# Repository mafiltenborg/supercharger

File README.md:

# BP-1A lookalike battery pack: BP-1M
**This is a Work In Progress. It's not even complete!**

If you own a vintage Texas Instruments calculator powered by a BP-1 or BP-1A pack of 3 rechargeable NiCd AA-sized cells in a plastic casing, this repo may be of interest to you.

Because none of these packs have survived the ravages of time, meaning lots of vintage calculators now need replacement battery packs. Yours too?

Here, you find my take on the subject. I've taken inspiration from a design made by Tom LeMense (aka *tomcircuit*) carrying the [CC-BY-SA licence](https://creativecommons.org/cc-licenses/), found here: https://github.com/tomcircuit/TI59_battery

Credit for the casing design goes to him!
The electronics also originate from tomcircuit, albeit in a different form factor and with some tweaks.

## Desired targets
I'm aiming for maximum capacity within the physical constraints given, USB-C charging and an on-off switch on the pack itself.
* Capacity: NiCd pack delivered 500 mAh, giving roughly 3 hours of on-time. I'd like to have a full working-day, meaning at least 1500 mAh.
* USB-C: The current charging standard. Also, the original charger delivers a maximum of 150 mA, leading to a theoretical charging time of at least 10 hours - more likely 'overnight'. Going with something like 500 mA would reduce charging time to 4 or 5 hours in the real world.
* Charging indicator LED. Takes the guesswork out of the refill-process.
* On-off switch: I'd like to take the strain off of the built-in slide switch.
* Charge state indicator; push a button and get indication on a tiny three-colour LED-bar
* Finally, it's dawned on me (greetings go to tomcircuit) that it's possible to make the design so that the calculator can be run off of the OE charger with the pack installed. A combo of practicality and foolproofing; I like that!

## Unachievable, unselected or unwanted targets
* Charging installed pack by means of the OE charger. Possible in theory, but we'd have to accept at least a 10-hour charging period - with the calculator off. Also, I'm doubtful if there's room for the extra circuitry.

## Additional thoughts & ideas
A charging stand to fit the TI59. Should be achievable as the pack's USB-C is pointing straight down. Could also be executed with magnetic pogo-pin-coupling. Hmmm...

## A few specifics on the design
Charger: LTH7R
Charge state display: HM1160

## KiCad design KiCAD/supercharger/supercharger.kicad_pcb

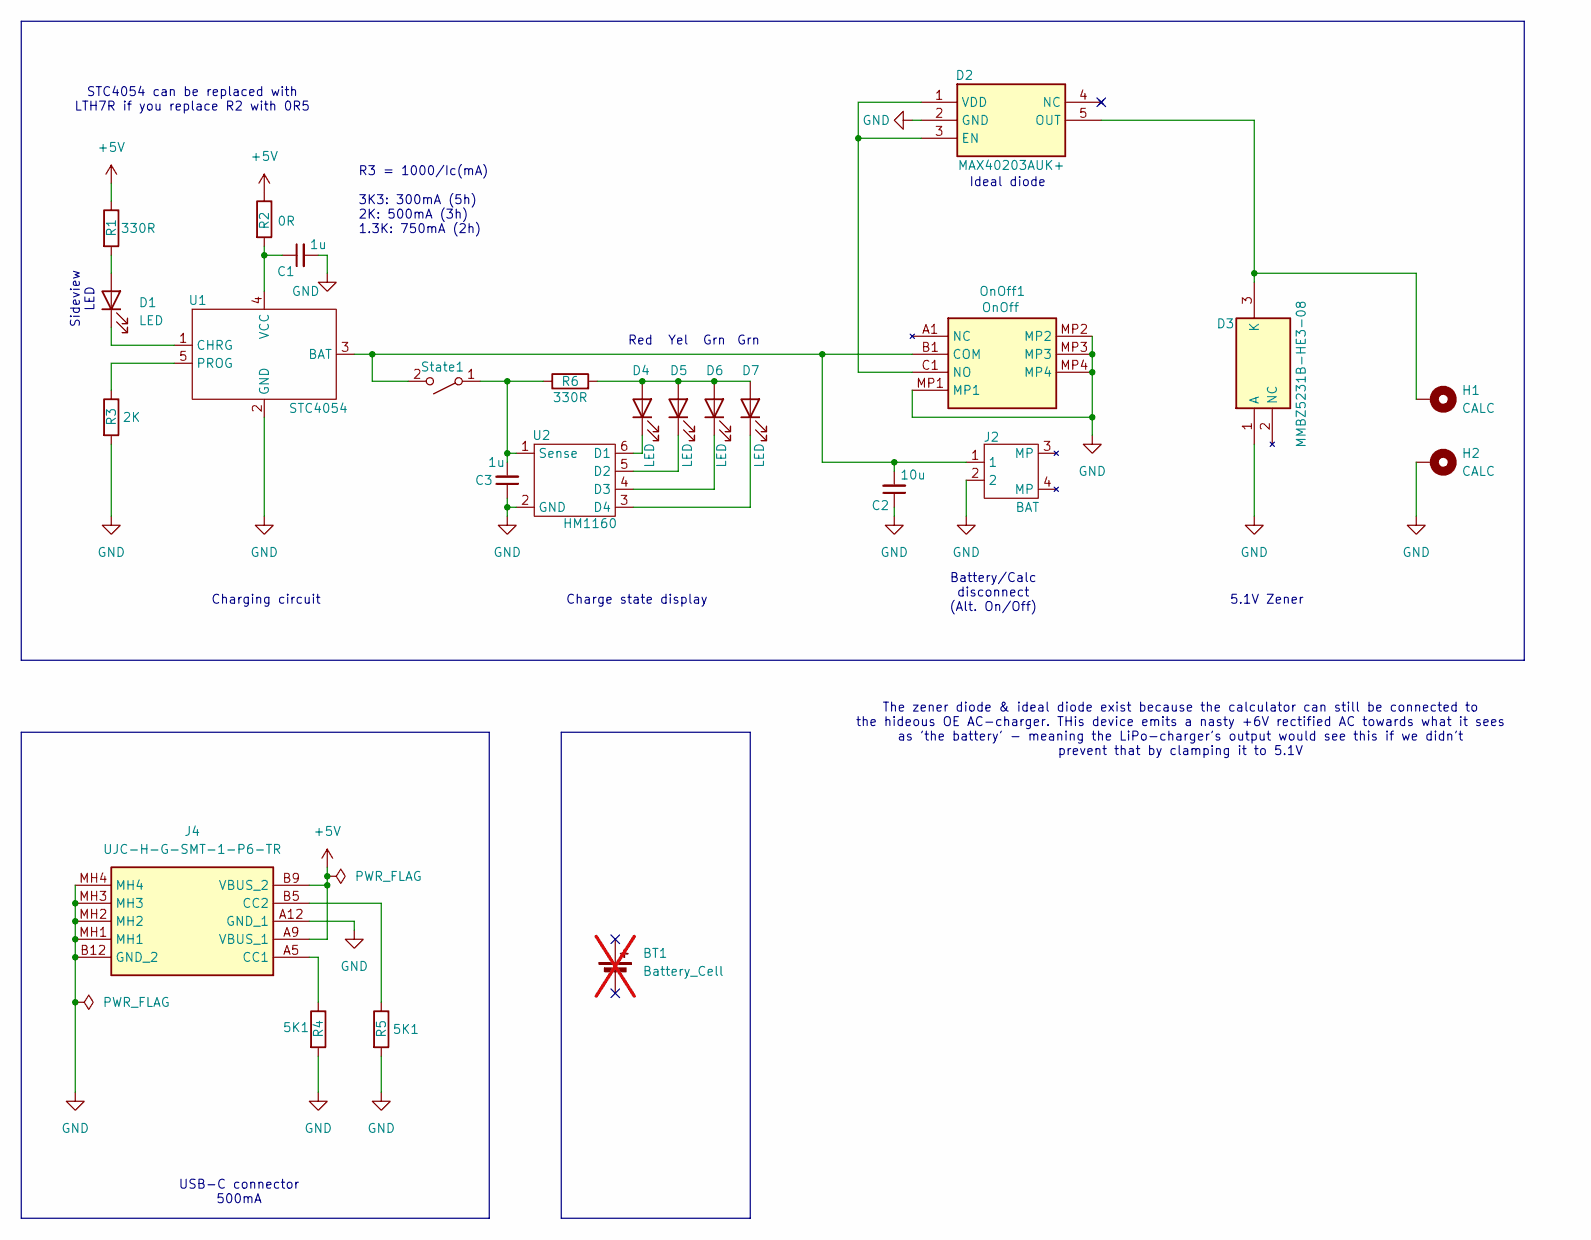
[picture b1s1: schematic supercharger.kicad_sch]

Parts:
BT1: Battery_Cell; not fitted
C1, C3: 1u; C_0603_1608Metric
C2: 10u; C_0603_1608Metric
D1, D4, D5, D6, D7: LED; LED_0603_1608Metric
D2: MAX40203AUK+; SOT-23-5_HandSoldering; Manufacturer_Part_Number MAX40203AUK+; Mouser Part Number 700-MAX40203AUK+
D3: MMBZ5231B-HE3-08; SOT-23-3; Manufacturer_Part_Number MMBZ5231B-HE3-08; Mouser Part Number 78-MMBZ5231B-HE3-08
H1, H2: CALC; TestPoint_THTPad_D1.5mm_Drill0.7mm
J2: BAT; Connector JST PH 1.25mm horizontal
J4: UJC-H-G-SMT-1-P6-TR; UJCHGSMT1P6TR; Manufacturer_Part_Number UJC-H-G-SMT-1-P6-TR
OnOff1: OnOff; MSK12C02; Manufacturer_Part_Number MSK12C02
R1, R6: 330R; R_0603_1608Metric
R2: 0R; R_0805_2012Metric
R3: 2K; R_0603_1608Metric
R4, R5: 5K1; R_0603_1608Metric
State1: State; B3U3000PMB
U1: STC4054; TSOT-23-5_HandSoldering
U2: HM1160; TSOT-23-6_HandSoldering

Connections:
+5V: J4.A9 (VBUS_1), J4.B9 (VBUS_2), R1.1, R2.1
GND: C1.2, C2.1, C3.1, D2.2 (GND), D3.1 (A), H2.1, J2.2, J4.A12 (GND_1), J4.B12 (GND_2), J4.MH1, J4.MH2, J4.MH3, J4.MH4, OnOff1.MP1, OnOff1.MP2, OnOff1.MP3, OnOff1.MP4, R3.2, R4.2, R5.2, U1.2 (GND), U2.2 (GND)
unnamed: D1.2 (A), R1.2
unnamed: D1.1 (K), U1.1 (CHRG)
unnamed: D2.1 (VDD), D2.3 (EN), OnOff1.C1 (NO)
unnamed: D2.5 (OUT), D3.3 (K), H1.1
unnamed: D4.2 (A), D5.2 (A), D6.2 (A), D7.2 (A), R6.2
unnamed: D4.1 (K), U2.6 (D1)
unnamed: D5.1 (K), U2.5 (D2)
unnamed: D6.1 (K), U2.4 (D3)
unnamed: D7.1 (K), U2.3 (D4)
unnamed: J4.A5 (CC1), R4.1
unnamed: J4.B5 (CC2), R5.1
unnamed: C2.2, J2.1, OnOff1.B1 (COM), State1.2 (B), U1.3 (BAT)
unnamed: C3.2, R6.1, State1.1 (A), U2.1 (Sense)
unnamed: R3.1, U1.5 (PROG)
unnamed: C1.1, R2.2, U1.4 (VCC)

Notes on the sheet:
Red
Grn
Sideview LED
Yel
R3 = 1000/Ic(mA) 3K3: 300mA (5h) 2K: 500mA (3h) 1.3K: 750mA (2h)
Battery/Calc disconnect (Alt. On/Off)
Ideal diode
STC4054 can be replaced with LTH7R if you replace R2 with 0R5
The zener diode & ideal diode exist because the calculator can still be connected to the hideous OE AC-charger. THis device emits a nasty +6V rectified AC towards what it sees as 'the battery' - meaning the LiPo-charger's output would see this if we didn't prevent that by clamping it to 5.1V
USB-C connector 500mA
Charge state display
Charging circuit
5.1V Zener

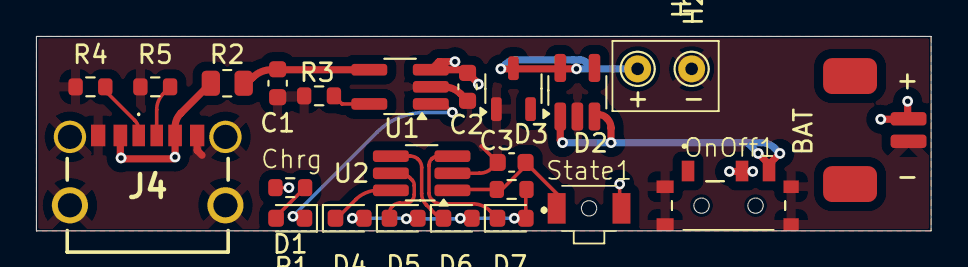
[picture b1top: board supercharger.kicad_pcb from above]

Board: 2 copper layers, 49.7 x 10.8 mm, 24 parts (0 on the bottom side), 17 nets.

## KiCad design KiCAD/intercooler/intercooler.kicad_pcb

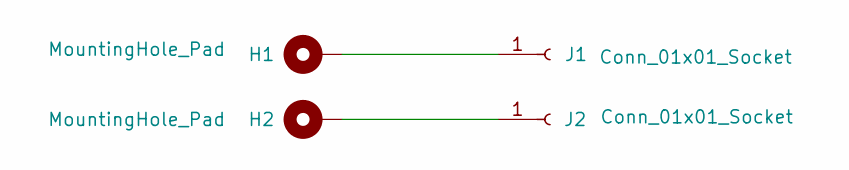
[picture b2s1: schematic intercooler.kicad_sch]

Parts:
H1, H2: MountingHole_Pad; TestPoint_THTPad_D1.5mm_Drill0.7mm
J1, J2: Conn_01x01_Socket; TI59-batterypad

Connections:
unnamed: H1.1, J1.1
unnamed: H2.1, J2.1

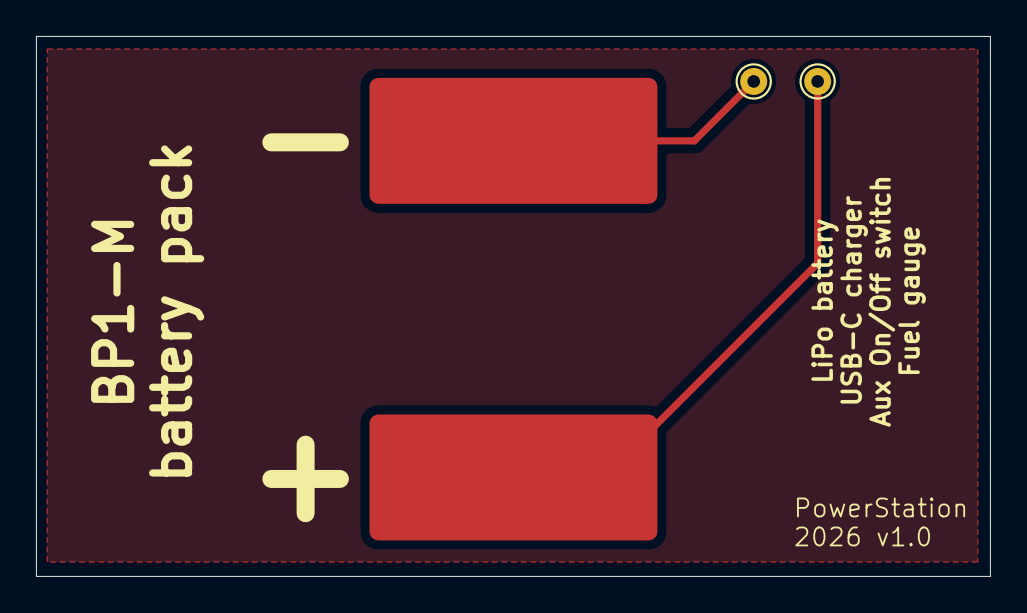
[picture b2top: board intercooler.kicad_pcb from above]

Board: 2 copper layers, 53.0 x 30.0 mm, 4 parts (0 on the bottom side), 2 nets.

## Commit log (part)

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2026-05-01 Add Readme
2026-05-01 Update README, remove bad type of license
2026-05-01 Readme: Reasons clarified
2026-05-01 wording
2026-05-01 Create LICENSE
    I go for GPL v3.0
2026-05-01 Update licensing terms in README
2026-06-03 README.md update
2026-06-19 Add buttons + charge display. Still need better/smaller connectors
2026-06-19 Reformulate - again - the Readme to provide a clearer path for the reader
2026-06-23 Rearrange components, add the elusive JST 1.25mm 2-pole connector (DIY).
2026-06-23 Add picture, update Readme including the Charge indicator
2026-06-24 Remove double statement from README
2026-06-24 Add 3D-print lid dummy
2026-06-24 Add text to photo
2026-06-24 Move photo to section describing the actual features of the device
2026-06-25 Move USB-C towards side by 1mm, tweak component placement, Add lid and PCB dummies
2026-06-26 Add the board that feeds power to the 'engine': intercooler
2026-06-26 Update supercharger with wired interconnect to intercooler.
2026-06-26 v1.0: Bestilt hos JLCPCB 260626
2026-06-26 Fabrication-toolkit-options added
2026-06-26 Update README with pictures of Intercooler. Also, changed PCB stackup to use 0.8mm PCB
2026-06-26 Oops - removed unwanted text on Intercooler battery-pads
2026-06-26 Add charging plinth proposal (thinking out loud)
